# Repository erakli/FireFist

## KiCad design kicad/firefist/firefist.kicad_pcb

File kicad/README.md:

# KiCAD схемы

Чтобы добавить Arduino Pro Mini, нужно вот эти два pull request'а к себе сохранить:

- https://github.com/KiCad/kicad-footprints/pull/1690/files -> C:\Program Files\KiCad\share\kicad\modules
- https://github.com/KiCad/kicad-symbols/pull/2028/files -> C:\Program Files\KiCad\share\kicad\library

https://docs.kicad-pcb.org/5.1.5/en/getting_started_in_kicad/getting_started_in_kicad.html

## Настройка отображения питания

https://electronics.stackexchange.com/a/438109

ref: https://electronics.stackexchange.com/a/417989

You tell KiCad where the power comes from by using the so called PWR_FLAG symbol.

The PWR_FLAG symbol has only one purpose. It tells KiCad that the net it is connected to has a power supply on it. Connect it as near as possible to the point where you connect power to the board to make it as useful as possible for finding problems in your schematic. (Directly at the connector that will be used to supply power.) If you have passive components in series between a power supply and the power consumer then you need to place another flag after that passive component. (Example if you have a fuse, the inductor of a filter, ...)

The PWR_FLAG symbol does not replace normal power symbols. Normal power symbols are global labels, the PWR_FLAG symbol does not add a label to the net!

Alternatively you create project specific symbols for the connectors that supply your board. (give the pins the electrical type "power output")

More details:

    https://forum.kicad.info/t/errtype-3-pin-connected-to-some-others-pins-but-no-pin-to-drive-it/10946/
    KiCAD 5 --- what is the significance of the various GND symbols?
    https://forum.kicad.info/t/electrical-type-of-schematic-symbol-pins/9439

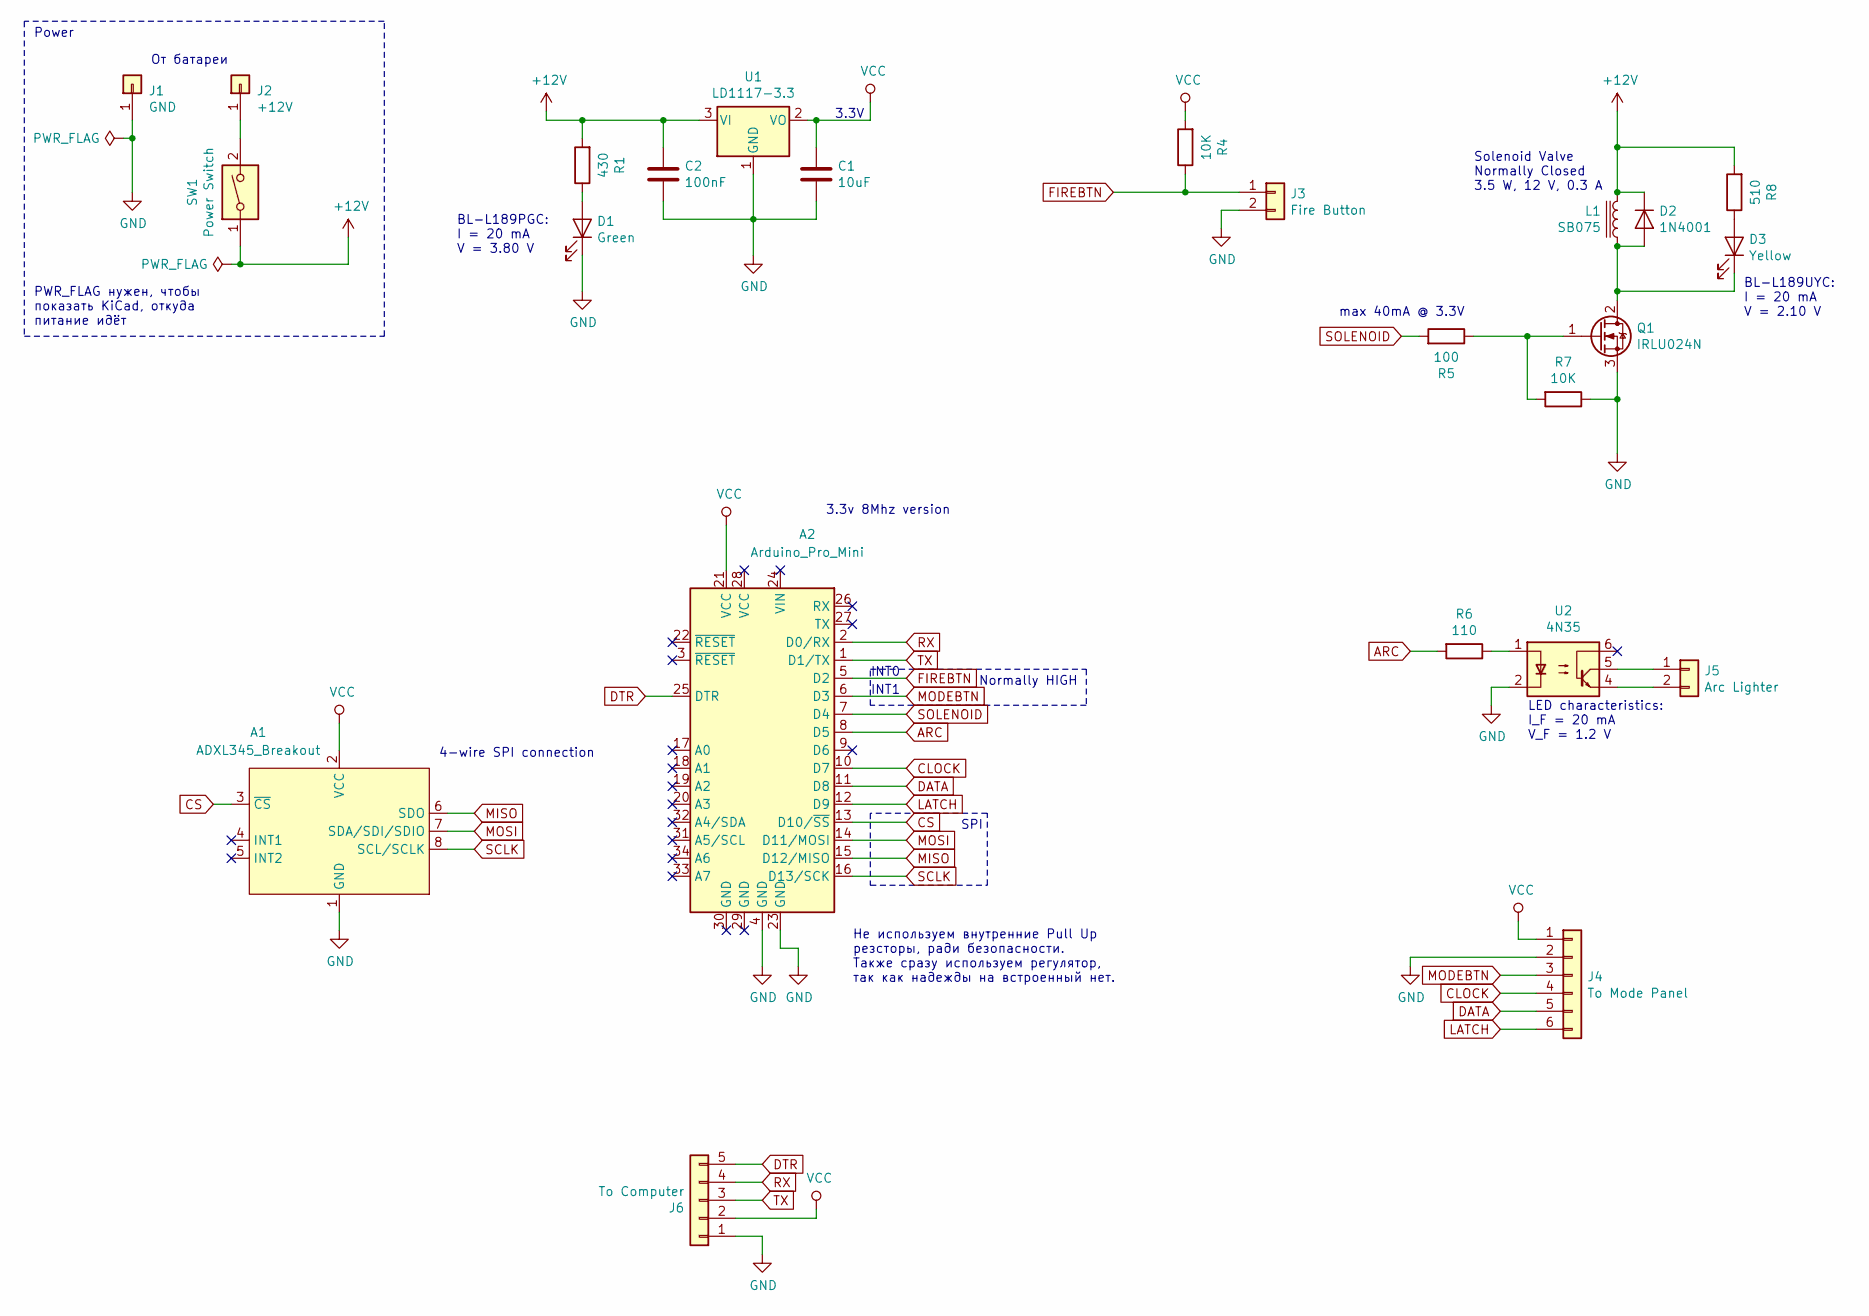
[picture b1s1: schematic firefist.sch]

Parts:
A1: ADXL345_Breakout
A2: Arduino_Pro_Mini
C1: 10uF; C_Disc_D3.0mm_W1.6mm_P2.50mm
C2: 100nF; C_Disc_D3.0mm_W1.6mm_P2.50mm
D1: Green; LED_D1.8mm_W3.3mm_H2.4mm
D2: 1N4001; D_DO-41_SOD81_P10.16mm_Horizontal
D3: Yellow; LED_D1.8mm_W3.3mm_H2.4mm
J1: GND; SolderWirePad_1x01_Drill0.8mm
J2: +12V; SolderWirePad_1x01_Drill0.8mm
J3: Fire Button; JST_XH_B2B-XH-A_1x02_P2.50mm_Vertical
J4: To Mode Panel; JST_EH_S6B-EH_1x06_P2.50mm_Horizontal
J5: Arc Lighter; JST_XH_B2B-XH-A_1x02_P2.50mm_Vertical
J6: To Computer; PinHeader_1x05_P2.54mm_Horizontal
L1: SB075; SolderWirePad_1x02_P3.81mm_Drill0.8mm
Q1: IRLU024N; TO-251-3-1EP_Horizontal_TabDown
R1: 430; R_Axial_DIN0207_L6.3mm_D2.5mm_P10.16mm_Horizontal
R4, R7: 10K; R_Axial_DIN0207_L6.3mm_D2.5mm_P10.16mm_Horizontal
R5: 100; R_Axial_DIN0207_L6.3mm_D2.5mm_P10.16mm_Horizontal
R6: 110; R_Axial_DIN0207_L6.3mm_D2.5mm_P10.16mm_Horizontal
R8: 510; R_Axial_DIN0207_L6.3mm_D2.5mm_P10.16mm_Horizontal
SW1: Power Switch; JST_EH_B2B-EH-A_1x02_P2.50mm_Vertical
U1: LD1117-3.3; TO-220-3_Horizontal_TabDown
U2: 4N35; DIP-6_W7.62mm

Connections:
+12V: C2.1, D2.1 (K), L1.1, R1.2, R8.2, SW1.1, U1.3 (VI)
ARC: A2.8 (D5), R6.2
CLOCK: A2.10 (D7), J4.4
CS: A1.3 (~CS), A2.13 (D10/~SS)
DATA: A2.11 (D8), J4.5
DTR: A2.25 (DTR), J6.5
FIREBTN: A2.5 (D2), J3.1, R4.1
GND: A1.1 (GND), A2.4 (GND), A2.23 (GND), C1.2, C2.2, D1.1 (K), J1.1, J3.2, J4.2, J6.1, Q1.3 (S), R7.1, U1.1 (GND), U2.2
LATCH: A2.12 (D9), J4.6
MISO: A1.6 (SDO), A2.15 (D12/MISO)
MODEBTN: A2.6 (D3), J4.3
MOSI: A1.7 (SDA/SDI/SDIO), A2.14 (D11/MOSI)
unnamed: D1.2 (A), R1.1
unnamed: D2.2 (A), D3.1 (K), L1.2, Q1.2 (D)
unnamed: D3.2 (A), R8.1
unnamed: J2.1, SW1.2
unnamed: J5.1, U2.5
unnamed: J5.2, U2.4
unnamed: Q1.1 (G), R5.1, R7.2
unnamed: R6.1, U2.1
RX: A2.2 (D0/RX), J6.4
SCLK: A1.8 (SCL/SCLK), A2.16 (D13/SCK)
SOLENOID: A2.7 (D4), R5.2
TX: A2.1 (D1/TX), J6.3
VCC: A1.2 (VCC), A2.21 (VCC), C1.1, J4.1, J6.2, R4.2, U1.2 (VO)

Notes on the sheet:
3.3v 8Mhz version
LED characteristics: I_F = 20 mA V_F = 1.2 V
BL-L189PGC: I = 20 mA V = 3.80 V
Не используем внутренние Pull Up резсторы, ради безопасности. Также сразу используем регулятор, так как надежды на встроенный нет.
Power
От батареи
PWR_FLAG нужен, чтобы показать KiCad, откуда питание идёт
INT0
INT1
Normally HIGH
3.3V
4-wire SPI connection
SPI
max 40mA @ 3.3V
Solenoid Valve Normally Closed 3.5 W, 12 V, 0.3 A
BL-L189UYC: I = 20 mA V = 2.10 V

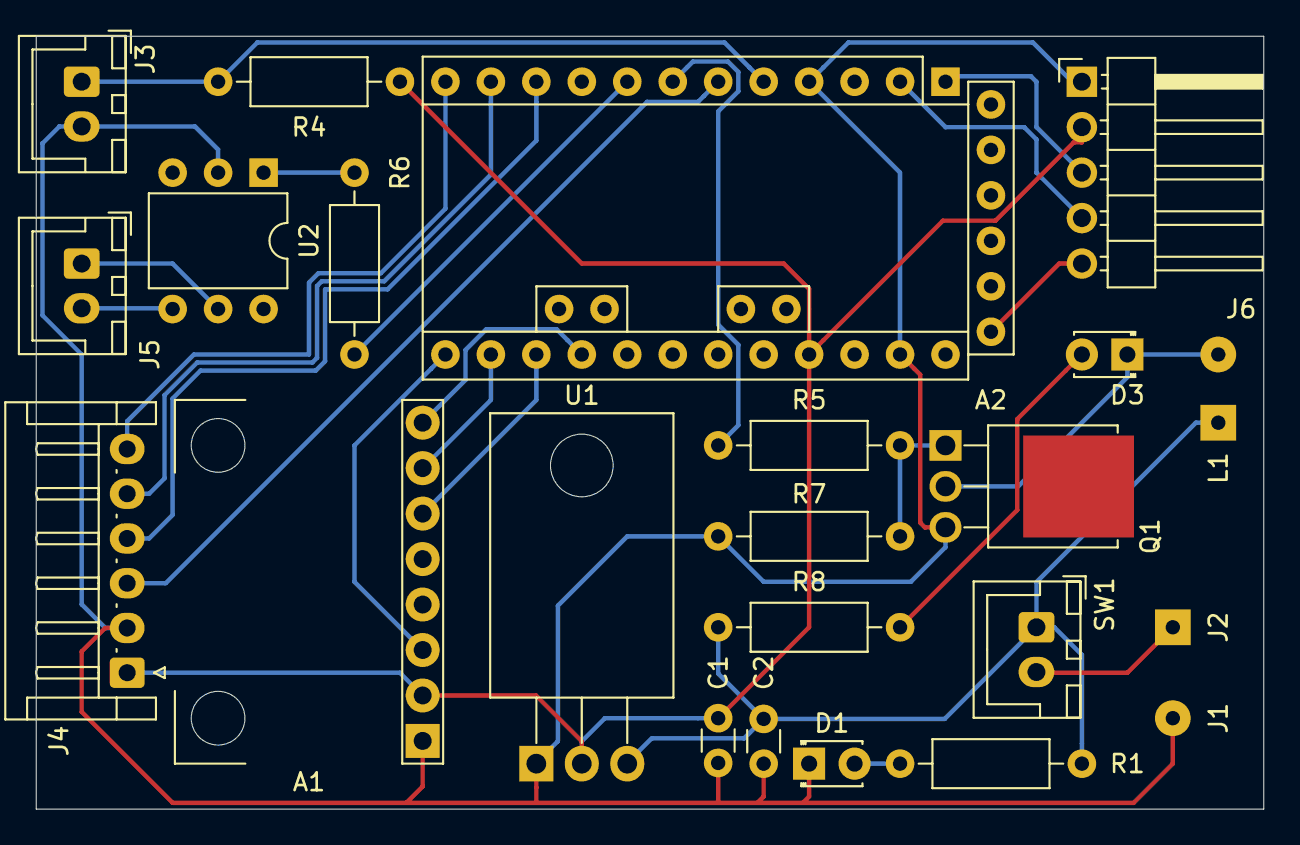
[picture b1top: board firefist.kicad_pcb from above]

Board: 2 copper layers, 68.6 x 43.2 mm, 23 parts (0 on the bottom side), 25 nets.
